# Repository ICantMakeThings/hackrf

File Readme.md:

# Updated USB-C

##### Added USB type C to the pcb, have not eddited anything else.

# HackRF

This repository contains hardware designs and software for HackRF,
a low cost, open source Software Defined Radio platform.

(photo by fd0 from https://github.com/fd0/hackrf-one-pictures)

principal author: Michael Ossmann <mike@ossmann.com>

Information on HackRF and purchasing HackRF: https://greatscottgadgets.com/hackrf/

--------------------

# Documentation

Documentation for HackRF can be viewed on [Read the Docs](https://hackrf.readthedocs.io/en/latest/). The raw documentation files for HackRF are in the [docs folder](https://github.com/mossmann/hackrf/tree/master/docs) in this repository and can be built locally by installing [Sphinx Docs](https://www.sphinx-doc.org/en/master/usage/installation.html) and running `make html`. Documentation changes can be submitted through pull request and suggestions can be made as GitHub issues. 

To create a PDF of the HackRF documentation from the HackRF repository while on Ubuntu:
* run `sudo apt install latexmk texlive-latex-extra`
* navigate to hackrf/docs on command line
* run the command `make latex`
* run the command `make latexpdf`

--------------------

# Getting Help

Before asking for help with HackRF, check to see if your question is listed in the [FAQ](https://hackrf.readthedocs.io/en/latest/faq.html).

For assistance with HackRF general use or development, please look at the [issues on the GitHub project](https://github.com/greatscottgadgets/hackrf/issues). This is the preferred place to ask questions so that others may locate the answer to your question in the future.

We invite you to join our community discussions on [Discord](https://discord.gg/rsfMw3rsU8). Note that while technical support requests are welcome here, we do not have support staff on duty at all times. Be sure to also submit an issue on GitHub if you've found a bug or if you want to ensure that your request will be tracked and not overlooked.

If you wish to see past discussions and questions about HackRF, you may also view the [mailing list archives](https://pairlist9.pair.net/pipermail/hackrf-dev/).

GitHub issues on this repository that are labelled "technical support" by Great Scott Gadgets employees can expect a response time of two weeks. We currently do not have expected response times for other GitHub issues or pull requests for this repository.

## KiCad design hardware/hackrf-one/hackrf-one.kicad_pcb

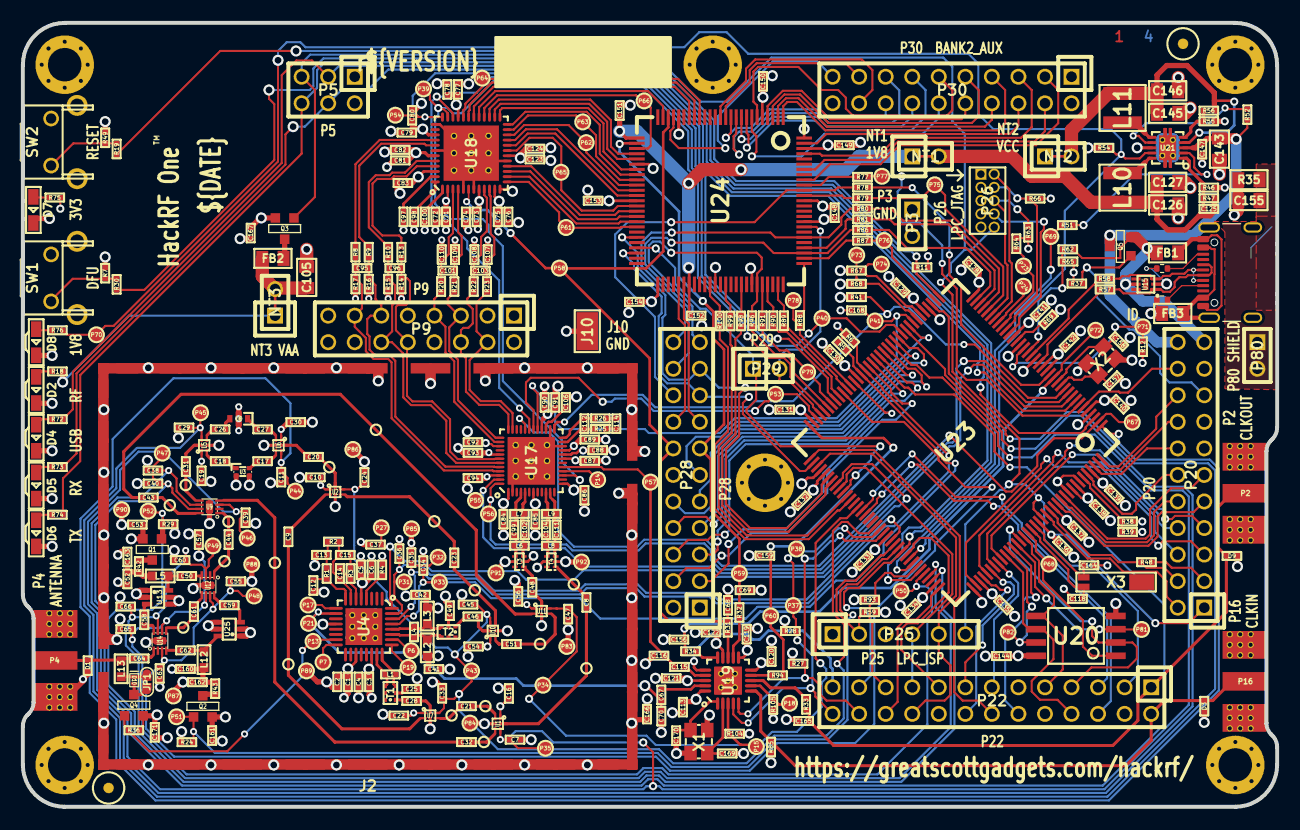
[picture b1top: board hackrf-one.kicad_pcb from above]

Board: 4 copper layers, 120.0 x 75.0 mm, 436 parts (0 on the bottom side), 317 nets.

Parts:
C1, C3, C5, C7, C11, C24, C29, C33, C34, C35, C36, C37, C38, C39, C40, C45, C47, C55, C57, C60, C63, C65, C66, C67, C115, C125: 33pF; GSG-0402
C2, C4, C6, C10, C16, C19, C22, C30, C54, C56, C87, C88, C89, C92, C93, C162, C163: 10nF; GSG-0402
C8, C21, C32, C43, C48, C51, C84, C85, C86, C94, C95, C96, C99, C101, C102, C103, C107, C108, C109, C110: 22pF; GSG-0402
C9, C17, C18, C20, C23, C25, C28, C31, C44, C46, C49, C50, C58, C59, C61, C62, C64, C71, C73, C75, C77, C79, C81, C83, C91, C113, C119, C120, C121, C122, C123, C128, C129, C130, C131, C132, C133, C134, C135, C136, C137, C138, C139, C140, C141, C142, C144, C147, C148, C149, C150, C151, C152, C153, C154, C166, C167: 100nF; GSG-0402
C12, C13: 330pF; GSG-0402
C14: 8p2; GSG-0402
C15, C112: 180pF; GSG-0402
C26, C27, C116, C156: 47pF; GSG-0402
C41, C42, C52, C68, C69, C70, C90, C159, C160, C165, C168: 100pF; GSG-0402
C53, C106, C161, C171: 1uF; GSG-0402
C72, C74, C76, C78, C80, C82, C124: 2.2uF; GSG-0402
C97, C98, C100: 330nF; GSG-0402
C104, C111: 3pF; GSG-0402
C105, C126, C127, C143, C145, C146: 10uF; GSG-0805
C114: 3.3nF; GSG-0402
C118, C157, C158, C164: 18pF; GSG-0402
C155: DNP; GSG-0805
C169, C170: 1.8pF; GSG-0402
D1, D3, D9: GSG-DIODE-TVS-BI; GSG-0402
D2: VAALED; LTST-S220
D4: USBLED; LTST-S220
D5: RXLED; LTST-S220
D6: TXLED; LTST-S220
D7: VCCLED; LTST-S220
D8: 1V8LED; LTST-S220
D10: D_Schottky; DSN1006-2
FB1, FB2, FB3: FILTER; GSG-0805
FID1, FID2: FIDUCIAL; GSG-MARK1MM
J2: RF-SHIELD-FRAME; GSG-SHIELD-BMI-S-230
J4, J5, J6, J7, J8, J9: MOUNTING_HOLE; GSG-HOLE126MIL-COPPER
J10: GND_CLIP; GSG-TEST-POINT-S1751-46R
JP1: Jumper; 0603-JUMPER
L1, L4, L6, L8, L9: DNP; GSG-0402
L2, L3, L5, L12, L13: 10uH; GSG-0603
L7: 6.2nH; GSG-0402
L10, L11: 4u7; GSG-NRG4026
NT1: 1V8; HEADER-1x2-SHORTED
NT2: VCC; HEADER-1x2-SHORTED
NT3: VAA; HEADER-1x2-SHORTED
P2: CLKOUT; GSG-SMA-73251-2120
P3: GND; GSG-HEADER-NOMARK-1x2
P4: ANTENNA; GSG-SMA-73251-2120
P5: LEDS; GSG-HEADER-2x3
P6: GPO4; GSG-TESTPOINT-50MIL
P7: GPO2; GSG-TESTPOINT-50MIL
P9: BASEBAND; GSG-HEADER-2x8
P13: GPO1; GSG-TESTPOINT-50MIL
P14: XCVR_CLKOUT; GSG-TESTPOINT-50MIL
P15: INTR; GSG-TESTPOINT-50MIL
P16: CLKIN; GSG-SMA-73251-2120
P17: GPO6; GSG-TESTPOINT-50MIL
P18: OEB; GSG-TESTPOINT-50MIL
P19: GPO3; GSG-TESTPOINT-50MIL
P20: GPIO; GSG-HEADER-2x11
P21: REF_IN; GSG-TESTPOINT-50MIL
P22: I2S; GSG-HEADER-2x13
P23: DBGEN; GSG-TESTPOINT-50MIL
P24: TRST; GSG-TESTPOINT-50MIL
P25: LPC_ISP; GSG-HEADER-1x6
P26: LPC_JTAG; GSG-50MIL-HEADER-2x5-TH
P27: MIXER_SDATA; GSG-TESTPOINT-50MIL
P28: SD; GSG-HEADER-2x11
P29: CPLD_JTAG; GSG-HEADER-1x2
P30: BANK2_AUX; GSG-HEADER-2x10
P31: MIXER_SCLK; GSG-TESTPOINT-50MIL
P32: MIXER_ENX; GSG-TESTPOINT-50MIL
P33: MIXER_RESETX; GSG-TESTPOINT-50MIL
P34: MIX_BYPASS; GSG-TESTPOINT-50MIL
P35: !MIX_BYPASS; GSG-TESTPOINT-50MIL
P37: SCL; GSG-TESTPOINT-50MIL
P38: SDA; GSG-TESTPOINT-50MIL
P39: SSP1_SCK; GSG-TESTPOINT-50MIL
P40: SSP1_COPI; GSG-TESTPOINT-50MIL
P41: SSP1_CIPO; GSG-TESTPOINT-50MIL
P43: RX; GSG-TESTPOINT-50MIL
P44: HP; GSG-TESTPOINT-50MIL
P45: LP; GSG-TESTPOINT-50MIL
P46: TX_MIX_BP; GSG-TESTPOINT-50MIL
P47: RX_MIX_BP; GSG-TESTPOINT-50MIL
P48: TX_AMP; GSG-TESTPOINT-50MIL
P49: RX_AMP; GSG-TESTPOINT-50MIL
P50: AMP_BYPASS; GSG-TESTPOINT-50MIL
P51: !TX_AMP_PWR; GSG-TESTPOINT-50MIL
P52: !RX_AMP_PWR; GSG-TESTPOINT-50MIL
P53: CS_XCVR; GSG-TESTPOINT-50MIL
P54: CS_AD; GSG-TESTPOINT-50MIL
P55: TXENABLE; GSG-TESTPOINT-50MIL
P56: RXENABLE; GSG-TESTPOINT-50MIL
P57: XTAL2; GSG-TESTPOINT-50MIL
P58: GCK1; GSG-TESTPOINT-50MIL
P59: GCK2; GSG-TESTPOINT-50MIL
P60: SGPIO_CLK; GSG-TESTPOINT-50MIL
P61: DA0; GSG-TESTPOINT-50MIL
P62: DA7; GSG-TESTPOINT-50MIL
P63: DD0; GSG-TESTPOINT-50MIL
P64: DD9; GSG-TESTPOINT-50MIL
P65: DA4; GSG-TESTPOINT-50MIL
P66: DD5; GSG-TESTPOINT-50MIL
P67: RSSI; GSG-TESTPOINT-50MIL
P68: SPIFI_CS; GSG-TESTPOINT-50MIL
P69: VREGMODE; GSG-TESTPOINT-50MIL
P70: EN_1V8; GSG-TESTPOINT-50MIL
P71: ID; GSG-TESTPOINT-50MIL
P72: GP_CLKIN; GSG-TESTPOINT-50MIL
P73: P1_2; GSG-TESTPOINT-50MIL
P74: P1_1; GSG-TESTPOINT-50MIL
P75: SGPIO0; GSG-TESTPOINT-50MIL
P76: SGPIO7; GSG-TESTPOINT-50MIL
P77: SGPIO9; GSG-TESTPOINT-50MIL
P78: SGPIO10; GSG-TESTPOINT-50MIL
P79: SGPIO11; GSG-TESTPOINT-50MIL
P80: SHIELD; GSG-HEADER-NOMARK-1x2
P81: SPIFI_SIO2; GSG-TESTPOINT-50MIL
P82: SPIFI_SIO3; GSG-TESTPOINT-50MIL
P83, P84, P85, P86, P87, P88, P89, P90, P91, P92: GND; GSG-TESTPOINT-50MIL
Q1, Q2, Q3, Q4, Q5: MOSFET_P; SOT23-3
R1, R2, R72, R75: 470; GSG-0402
R3: 22k; GSG-0402
R4: 51k; GSG-0402
R5, R6, R7, R11, R12, R24, R29, R36, R37, R41, R48, R49, R51, R52, R54, R59, R62, R63, R64, R66, R67, R68, R85, R93, R104, R105: 10k; GSG-0402
R8, R9, R10, R13, R73, R76: 1k; GSG-0402
R14, R15, R16, R17: 4k7; GSG-0402
R18, R27, R28, R74: 1k8; GSG-0402
R19, R30, R31, R32, R33, R34, R77, R78, R79, R80, R81, R86, R87, R88, R89, R90, R91, R94, R96, R98, R99, R100: 39; GSG-0402
R20, R21, R22, R23, R57, R58: 0; GSG-0402
R25, R26: 475; GSG-0402
R35: DNP; GSG-0805
R38: 15.4k; GSG-0402
R39, R47: 330k; GSG-0402
R42, R43: 18; GSG-0402
R46, R55: 162k; GSG-0402
R56: 715k; GSG-0402
R65: 18k; GSG-0402
R69: 12k; GSG-0402
SW1: DFU; GSG-SWITCH-FSMRA
SW2: RESET; GSG-SWITCH-FSMRA
T1: MIX_IN_BALUN; GSG-B0310J50100AHF
T2: MIX_OUT_BALUN; GSG-B0310J50100AHF
T3: RX_BALUN; GSG-2500BL14M100
T4: TX_BALUN; GSG-2500BL14M100
TESTPOINT-30MIL-MASKONLY, TESTPOINT-30MIL-MASKONLY#2, TESTPOINT-30MIL-MASKONLY#3, TESTPOINT-30MIL-MASKONLY#4, TESTPOINT-30MIL-MASKONLY#5, TESTPOINT-30MIL-MASKONLY#6, TESTPOINT-30MIL-MASKONLY#7, TESTPOINT-30MIL-MASKONLY#8, TESTPOINT-30MIL-MASKONLY#9, TESTPOINT-30MIL-MASKONLY#10, TESTPOINT-30MIL-MASKONLY#11, TESTPOINT-30MIL-MASKONLY#12, TESTPOINT-30MIL-MASKONLY#13, TESTPOINT-30MIL-MASKONLY#14, TESTPOINT-30MIL-MASKONLY#15, TESTPOINT-30MIL-MASKONLY#16, TESTPOINT-30MIL-MASKONLY#17: VAL**; GSG-TESTPOINT-30MIL-MASKONLY
U1, U2, U5, U6, U7, U10, U11: SKY13453; SKY13350-385LF
U3: LOWPASS_FILTER; GSG-LP0603
U4: RFFC5072; GSG-QFN32
U8: HIGHPASS_FILTER; GSG-HP-DEA
U9, U12, U14: SKY13317; GSG-SKY13317-373LF
U13, U25: MGA-81563; GSG-SOT363
U15: TVS; GSG-LXES1TBCC2-004
U17: MAX2837; GSG-QFN48-6
U18: MAX5864; GSG-QFN48-7
U19: SI5351C; GSG-QFN20-4
U20: W25Q80; GSG-SOIC8-208
U21: TPS62410; GSG-S-PVSON-N10
U23: LPC4320FBD144; GSG-LQFP144
U24: GSG-XC2C64A-7VQG100C; GSG-VQ100
X1: MAIN_XTAL; GSG-XTAL3.2x2.5mm
X2: MCU_XTAL; GSG-XTAL3.2x2.5mm
X3: RTC_XTAL; GSG-XTAL-AB26TRQ

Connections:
!MIX_BYPASS: C7.2, C38.2, P35.1, U1.5 (VCTL), U9.6 (V2), U23.50 (P1_7)
!RX_AMP_PWR: P52.1, Q1.1 (G), R29.2, U23.106 (P2_12)
!TX_AMP_PWR: P51.1, Q2.1 (G), R24.1, U23.97 (P6_9)
!VAA_ENABLE: P5.5, Q3.1 (G), R11.2, U23.37 (P5_0)
+1V8: C151.1, C152.1, NT1.1, U24.26 (VCC), U24.57 (VCC)
/baseband/CLK0: R31.2, U19.13 (CLK0)
/baseband/CLK1: R32.2, U19.12 (CLK1)
/baseband/CLK2: R94.2, U19.9 (CLK2)
/baseband/CLK3: R33.2, U19.8 (CLK3)
/baseband/CLK5: C115.1, U19.17 (CLK5)
/baseband/COM: C97.1, U18.47 (COM)
/baseband/CPOUT+: C112.2, R25.1, U17.23 (CPOUT+)
/baseband/CPOUT-: C112.1, R26.1, U17.24 (CPOUT-)
/baseband/IA+: C101.1, C110.1, R20.1, U18.3 (IA+)
/baseband/IA-: C101.2, C109.1, R21.1, U18.4 (IA-)
/baseband/ID+: R13.1, U18.45 (ID+)
/baseband/ID-: R10.1, U18.44 (ID-)
/baseband/INTR: P15.1, R104.2, U19.3 (INTR)
/baseband/OEB: P18.1, R105.2, U19.7 (OEB)
/baseband/QA+: C103.2, C107.1, R23.1, U18.10 (QA+)
/baseband/QA-: C103.1, C108.1, R22.1, U18.9 (QA-)
/baseband/QD+: R8.1, U18.40 (QD+)
/baseband/QD-: R9.1, U18.41 (QD-)
/baseband/REFN: C98.1, U18.48 (REFN)
/baseband/REFP: C100.1, U18.1 (REFP)
/baseband/RXBBI+: P9.7, R20.2, U17.38 (RXBBI+)
/baseband/RXBBI-: P9.5, R21.2, U17.37 (RXBBI-)
/baseband/RXBBQ+: P9.6, R22.2, U17.36 (RXBBQ+)
/baseband/RXBBQ-: P9.4, R23.2, U17.35 (RXBBQ-)
/baseband/TXBBI+: C96.1, P9.12, R10.2, R15.1, U17.43 (TXBBI+)
/baseband/TXBBI-: C96.2, P9.10, R13.2, R14.1, U17.42 (TXBBI-)
/baseband/TXBBQ+: C95.2, P9.11, R9.2, R16.1, U17.44 (TXBBQ+)
/baseband/TXBBQ-: C95.1, P9.13, R8.2, R17.1, U17.45 (TXBBQ-)
/baseband/XA: C170.2, U19.1 (XA), X1.3
/baseband/XB: C169.2, U19.2 (XB), X1.1
/baseband/XCVR_CLKOUT: P14.1, U17.16 (CLOCKOUT)
/baseband/XTAL2: C115.2, C116.1, P57.1, U17.17 (XTAL2)
/frontend/!ANT_BIAS: P13.1, Q4.1 (G), R36.1, U4.15 (GPO1/ADD1)
/frontend/REF_IN: C67.2, C70.1, P21.1, U4.10 (REF_IN)
/frontend/RX_AMP_IN: C58.1, U14.8 (RF3)
/frontend/RX_AMP_OUT: C50.2, U12.4 (RF1)
/frontend/TX_AMP_IN: C59.1, U12.8 (RF3)
/frontend/TX_AMP_OUT: C62.1, U14.4 (RF1)
/mcu/usb/power/ADC0_0: P20.20, U23.6 (ADC0_0/ADC1_0/DAC)
/mcu/usb/power/ADC0_2: P20.16, U23.143 (ADC0_2/ADC1_2)
/mcu/usb/power/ADC0_3: R38.2, R39.1, U23.139 (ADC0_3/ADC1_3)
/mcu/usb/power/ADC0_5: P20.18, U23.144 (ADC0_5/ADC1_5)
/mcu/usb/power/ADC0_6: P20.14, U23.142 (ADC0_6/ADC1_6)
/mcu/usb/power/B1AUX13: P28.16, U24.55 (BANK1F4M13)
/mcu/usb/power/B1AUX14: P28.15, U24.56 (BANK1F4M14)
/mcu/usb/power/B2AUX1: P30.18, U24.13 (BANK2F1M1)
/mcu/usb/power/B2AUX2: P30.17, U24.12 (BANK2F1M2)
/mcu/usb/power/B2AUX3: P30.16, U24.11 (BANK2F1M3)
/mcu/usb/power/B2AUX4: P30.15, U24.10 (BANK2F1M4)
/mcu/usb/power/B2AUX5: P30.14, U24.9 (BANK2F1M5)
/mcu/usb/power/B2AUX6: P30.13, U24.8 (BANK2F1M6)
/mcu/usb/power/B2AUX7: P30.12, U24.7 (BANK2F1M7)
/mcu/usb/power/B2AUX8: P30.11, U24.6 (BANK2F1M8)
/mcu/usb/power/B2AUX9: P30.10, U24.4 (BANK2F1M9)
/mcu/usb/power/B2AUX10: P30.9, U24.3 (BANK2F1M10)
/mcu/usb/power/B2AUX11: P30.8, U24.2 (BANK2F1M11)
/mcu/usb/power/B2AUX12: P30.7, U24.1 (BANK2F1M12)
/mcu/usb/power/B2AUX13: P30.6, U24.99 (BANK2F1M13)
/mcu/usb/power/B2AUX14: P30.5, U24.97 (BANK2F1M14)
/mcu/usb/power/B2AUX15: P30.4, U24.94 (BANK2F1M15)
/mcu/usb/power/B2AUX16: P30.3, U24.92 (BANK2F1M16)
/mcu/usb/power/BANK2F3M1: R77.2, U24.91 (BANK2F3M1)
/mcu/usb/power/BANK2F3M2: P28.18, R78.2, U24.90 (BANK2F3M2)
/mcu/usb/power/BANK2F3M3: R79.2, U24.89 (BANK2F3M3)
/mcu/usb/power/BANK2F3M4: P28.22, R80.2, U24.81 (BANK2F3M4)
/mcu/usb/power/BANK2F3M5: R81.2, U24.79 (BANK2F3M5)
/mcu/usb/power/BANK2F3M6: P28.20, R86.2, U24.78 (BANK2F3M6)
/mcu/usb/power/BANK2F3M7: R87.2, U24.77 (BANK2F3M7)
/mcu/usb/power/BANK2F3M8: R88.2, U24.76 (BANK2F3M8)
/mcu/usb/power/BANK2F3M9: R89.2, U24.74 (BANK2F3M9)
/mcu/usb/power/BANK2F3M10: R90.2, U24.72 (BANK2F3M10)
/mcu/usb/power/BANK2F3M11: R91.2, U24.71 (BANK2F3M11)
/mcu/usb/power/BANK2F3M12: P28.21, R96.2, U24.70 (BANK2F3M12)
/mcu/usb/power/BANK2F3M14: R98.2, U24.67 (BANK2F3M14)
/mcu/usb/power/BANK2F3M15: R99.2, U24.64 (BANK2F3M15)
/mcu/usb/power/BANK2F3M16: R100.2, U24.61 (BANK2F3M16)
/mcu/usb/power/CPLD_TCK: P28.17, U23.74 (P6_1), U24.48 (TCK)
/mcu/usb/power/CPLD_TDI: P28.19, U23.78 (P6_2), U24.45 (TDI)
/mcu/usb/power/CPLD_TDO: P29.2, U23.69 (P9_5), U24.83 (TDO)
/mcu/usb/power/CPLD_TMS: P29.1, U23.82 (P6_5), U24.47 (TMS)
/mcu/usb/power/DBGEN: P23.1, R64.1, U23.28 (DBGEN)
/mcu/usb/power/DM: R58.1, U23.20 (USB0_DM)
/mcu/usb/power/DP: R57.1, U23.18 (USB0_DP)
/mcu/usb/power/EN1V8: P70.1, R54.2, R76.2, U21.9 (EN2), U23.100 (P6_10)
/mcu/usb/power/GCK0: P30.19, U24.22 (BANK1F2M7)
/mcu/usb/power/GPIO3_8: P20.5, U23.110 (P7_0)
/mcu/usb/power/GPIO3_9: P20.6, U23.113 (P7_1)
/mcu/usb/power/GPIO3_10: P20.7, U23.115 (P7_2)
/mcu/usb/power/GPIO3_11: P20.8, U23.117 (P7_3)
/mcu/usb/power/GPIO3_12: P20.9, U23.132 (P7_4)
/mcu/usb/power/GPIO3_13: P20.10, U23.133 (P7_5)
/mcu/usb/power/GPIO3_14: P20.11, U23.134 (P7_6)
/mcu/usb/power/GPIO3_15: P20.12, U23.140 (P7_7)
/mcu/usb/power/GP_CLKIN: C156.1, P72.1, R34.1, U23.14 (P4_7)
/mcu/usb/power/I2C1_SCL: P22.5, U23.88 (P2_4)
/mcu/usb/power/I2C1_SDA: P22.6, U23.87 (P2_3)
/mcu/usb/power/I2S0_RX_MCLK: P22.14, U23.73 (P6_0)
/mcu/usb/power/I2S0_RX_SCK: P22.12, U23.120 (PF_4)
/mcu/usb/power/I2S0_RX_SDA: P22.13, U23.116 (P3_2)
/mcu/usb/power/I2S0_RX_WS: P22.15, U23.114 (P3_1)
/mcu/usb/power/I2S0_TX_MCLK: P22.17, U23.99 (CLK2)
/mcu/usb/power/I2S0_TX_SCK: P22.16, U23.112 (P3_0)
/mcu/usb/power/ISP: P25.2, R59.2, U23.96 (P2_7)
/mcu/usb/power/LED1: P5.3, R72.2, U23.3 (P4_1)
/mcu/usb/power/LED2: P5.4, R73.2, U23.8 (P4_2)
/mcu/usb/power/LED3: P5.6, R74.2, U23.103 (P6_12)
/mcu/usb/power/P1_1: P74.1, R67.1, U23.42 (P1_1)
/mcu/usb/power/P1_2: P73.1, R68.1, U23.43 (P1_2)
/mcu/usb/power/P2_8: P22.23, R30.1, U23.98 (P2_8)
/mcu/usb/power/P2_9: P22.21, R93.1, U23.102 (P2_9)
/mcu/usb/power/P2_13: P22.22, U23.108 (P2_13)
/mcu/usb/power/REG_OUT1: C145.2, C146.2, L11.1, NT2.2, R56.1, U21.4 (FB1)
/mcu/usb/power/REG_OUT2: C125.1, C126.1, C127.1, L10.2, NT1.2, R47.1
/mcu/usb/power/RESET: P22.3, P25.6, P26.10, R19.1, U23.128 (RESET)
/mcu/usb/power/RREF: R69.1, U23.24 (USB0_RREF)
/mcu/usb/power/RTCX1: C118.1, U23.125 (RTCX1), X3.2
/mcu/usb/power/RTCX2: C164.1, U23.126 (RTCX2), X3.1
/mcu/usb/power/RTC_ALARM: P20.2, U23.129 (RTC_ALARM)
/mcu/usb/power/SD_CD: P28.3, U23.60 (P1_13)
/mcu/usb/power/SD_CLK: P28.11, U23.45 (CLK0)
/mcu/usb/power/SD_CMD: P28.9, U23.49 (P1_6)
/mcu/usb/power/SD_DAT0: P28.7, U23.52 (P1_9)
/mcu/usb/power/SD_DAT1: P28.6, U23.53 (P1_10)
/mcu/usb/power/SD_DAT2: P28.5, U23.55 (P1_11)
/mcu/usb/power/SD_DAT3: P28.4, U23.56 (P1_12)
/mcu/usb/power/SD_POW: P28.10, U23.48 (P1_5)
/mcu/usb/power/SD_VOLT0: P28.8, U23.51 (P1_8)
/mcu/usb/power/SGPIO0: P75.1, R79.1, U23.32 (P0_0)
/mcu/usb/power/SGPIO1: R81.1, U23.34 (P0_1)
/mcu/usb/power/SGPIO2: R89.1, U23.62 (P1_15)
/mcu/usb/power/SGPIO3: R90.1, U23.64 (P1_16)
/mcu/usb/power/SGPIO4: R98.1, U23.79 (P6_3)
/mcu/usb/power/SGPIO5: R99.1, U23.83 (P6_6)
/mcu/usb/power/SGPIO6: R100.1, U23.84 (P2_2)
/mcu/usb/power/SGPIO7: P76.1, R87.1, U23.38 (P1_0)
/mcu/usb/power/SGPIO9: P77.1, R77.1, U23.7 (P4_3)
/mcu/usb/power/SGPIO10: P78.1, R88.1, U23.61 (P1_14)
/mcu/usb/power/SGPIO11: P79.1, R91.1, U23.66 (P1_17)
/mcu/usb/power/SGPIO12: R96.1, U23.67 (P1_18)
/mcu/usb/power/SGPIO13: R78.1, U23.15 (P4_8)
/mcu/usb/power/SGPIO14: R80.1, U23.33 (P4_9)
/mcu/usb/power/SGPIO15: R86.1, U23.35 (P4_10)
/mcu/usb/power/SPIFI_CIPO: P22.7, U20.2 (DO), U23.122 (P3_6)
/mcu/usb/power/SPIFI_COPI: P22.9, U20.5 (DI), U23.123 (P3_7)
/mcu/usb/power/SPIFI_CS: P68.1, U20.1 (CS), U23.124 (P3_8)
/mcu/usb/power/SPIFI_SCK: P22.8, U20.6 (CLK), U23.118 (P3_3)
/mcu/usb/power/SPIFI_SIO2: P81.1, U20.3 (WP), U23.121 (P3_5)
/mcu/usb/power/SPIFI_SIO3: P82.1, U20.7 (HOLD), U23.119 (P3_4)
/mcu/usb/power/TCK: P26.4, R66.2, U23.27 (TCK/SWDCLK)
/mcu/usb/power/TDI: P26.8, U23.26 (TDI)
/mcu/usb/power/TDO: P26.6, R63.1, U23.31 (TDO/SWO)
/mcu/usb/power/TMS: P26.2, U23.30 (TMS/SWDIO)
/mcu/usb/power/U0_RXD: P22.19, P25.4, U23.81 (P2_1)
/mcu/usb/power/U0_TXD: P22.20, P25.5, U23.75 (P2_0)
/mcu/usb/power/USB_SHIELD: C155.1, P80.1, P80.2, R35.1
/mcu/usb/power/VBAT: C136.1, P20.1, U23.127 (VBAT)
/mcu/usb/power/VBUS: FB1.2, P20.21, Q5.2 (S), R62.2, U15.5 (VDD)
/mcu/usb/power/VBUSCTRL: P20.17, Q5.1 (G), R37.2
/mcu/usb/power/VIN: C143.1, C147.1, P20.22, Q5.3 (D), R52.1, U21.3 (VIN)
/mcu/usb/power/VREGMODE: P69.1, R51.2, U23.101 (P6_11)
/mcu/usb/power/WAKEUP: P20.4, R48.2, U23.130 (WAKEUP0)
/mcu/usb/power/XTAL1: C157.1, U23.12 (XTAL1), X2.1
/mcu/usb/power/XTAL2: C158.1, U23.13 (XTAL2), X2.3
AMP_BYPASS: C57.1, C65.2, P50.1, U12.6 (V2), U14.6 (V2), U23.104 (P2_10)
CLK6: P22.25, U19.16 (CLK6)
CLKIN: D3.2 (K), P16.1 (RF), P22.2, R85.1, U19.6 (CLKIN)
CLKOUT: C165.1, D9.2 (K), P2.1 (RF), P22.1, R33.1
CS_AD: P54.1, U18.36 (CS), U23.65 (P5_7)
CS_XCVR: P53.1, U17.30 (CS), U23.70 (P1_20)
DA0: P61.1, U18.13 (DA0), U24.43 (BANK1F4M8)
DA1: U18.14 (DA1), U24.42 (BANK1F4M7)
DA2: U18.15 (DA2), U24.41 (BANK1F4M6)
DA3: U18.16 (DA3), U24.40 (BANK1F4M5)
DA4: P65.1, U18.19 (DA4), U24.39 (BANK1F4M4)
DA5: U18.20 (DA5), U24.37 (BANK1F4M3)
DA6: U18.21 (DA6), U24.36 (BANK1F4M2)
DA7: P62.1, U18.22 (DA7), U24.35 (BANK1F4M1)
DD0: P63.1, U18.23 (DD0), U24.34 (BANK1F2M16)
DD1: U18.24 (DD1), U24.33 (BANK1F2M15)
DD2: U18.25 (DD2), U24.32 (BANK1F2M14)
DD3: U18.26 (DD3), U24.30 (BANK1F2M13)
DD4: U18.27 (DD4), U24.29 (BANK1F2M12)
DD5: P66.1, U18.28 (DD5), U24.28 (BANK1F2M11)
DD6: U18.29 (DD6), U24.24 (BANK1F2M9)
DD7: U18.30 (DD7), U24.19 (BANK1F2M6)
DD8: U18.31 (DD8), U24.18 (BANK1F2M5)
DD9: P64.1, U18.32 (DD9), U24.17 (BANK1F2M4)
GCK1: C68.1, P28.14, P58.1, R31.1, U18.6 (CLK), U24.23 (BANK1F2M8)
GCK2: C69.1, P28.13, P59.1, R32.1, U24.27 (BANK1F2M10)
GND: C1.2, C2.2, C3.2, C4.2, C5.2, C6.2, C7.1, C10.1, C11.1, C12.2, C13.2, C16.2, C19.1, C22.1, C24.1, C25.2, C29.2, C30.2, C33.2, C34.2, C35.2, C36.2, C37.2, C38.1, C39.1, C40.1, C41.2, C42.2, C45.1, C47.1, C49.1, C52.2, C53.2, C54.2, C55.2, C56.2, C57.2, C60.1, C63.2, C65.1, C66.1, C68.2, C69.2, C70.2, C71.2, C72.2, C73.2, C74.2, C75.2, C76.2, C77.2, C78.2, C79.2, C80.2, C81.2, C82.2, C83.2, C84.2, C85.2, C86.2, C87.2, C88.2, C89.2, C90.2, C91.2, C92.2, C93.2, C94.2, C97.2, C98.2, C100.2, C105.2, C106.2, C107.2, C108.2, C109.2, C110.2, C113.2, C116.2, C118.2, C119.2, C120.2, C121.2, C122.2, C123.2, C124.2, C126.2, C127.2, C128.2, C129.2, C130.2, C131.2, C132.2, C133.2, C134.2, C135.2, C136.2, C137.2, C138.2, C139.2, C140.2, C141.2, C142.2, C143.2, C144.2, C145.1, C146.1, C147.2, C148.2, C149.2, C150.2, C151.2, C152.2, C153.2, C154.2, C155.2, C156.2, C157.2, C158.2, C159.2, C160.2, C161.2, C162.1, C163.1, C164.2, C165.2, C166.2, C167.2, C168.2, C169.1, C170.1, C171.2, D1.1 (A), D2.1 (K), D3.1 (A), D4.1 (K), D5.1 (K), D6.1 (K), D7.1 (K), D8.1 (K), D9.1 (A), FB3.2, J2.0 (SHIELD), J4.1, J5.1, J6.1, J7.1, J8.1, J9.1, J10.1, P2.2 (GND), P3.1, P3.2, P4.2 (GND), P5.1, P9.1, P9.2, P9.3, P9.8, P9.9, P9.14, P9.15, P9.16, P16.2 (GND), P20.13, P20.15, P20.19, P22.4, P22.10, P22.18, P25.1, P26.3, P26.5, P26.9, P28.2, P28.12, P30.2, P30.20, P83.1, P84.1, P85.1, P86.1, P87.1, P88.1, P89.1, P90.1, P91.1, P92.1, R4.1, R7.2, R14.2, R15.2, R16.2, R17.2, R35.2, R37.1, R39.2, R41.1, R46.1, R54.1, R55.1, R65.1, R68.2, R69.2, R85.2, R93.2, SW1.0 (SHIELD), SW2.0 (SHIELD), SW2.1, T3.2 (PC), T3.5 (S2), T4.2 (PC), T4.5 (S2), U1.3 (GND), U2.3 (GND), U3.2 (GND), U3.3 (GND), U4.0 (EP), U4.12 (TM), U5.3 (GND), U6.3 (GND), U7.3 (GND), U8.2 (GND), U8.4 (GND), U9.0 (GND), U10.3 (GND), U11.3 (GND), U12.0 (GND), U13.1 (GND), U13.2 (GND), U13.4 (GND), U13.5 (GND), U14.0 (GND), U15.2 (GND), U17.0 (EP), U17.2 (GNDRXLNA), U17.22 (GNDCP), U17.26 (GNDVCO), U18.0 (EP), U18.5 (GND), U18.7 (GND), U18.12 (GND), U18.17 (OGND), U18.37 (GND), U18.42 (GND), U19.0 (GND), U20.4 (GND), U21.0 (PP), U21.8 (GND), U23.4 (VSSIO), U23.19 (USB0_VSSA_TERM), U23.23 (USB0_VSSA_REF), U23.40 (VSSIO), U23.76 (VSSIO), U23.109 (VSSIO), U23.135 (VSSA), U23.138 (ADC0_4/ADC1_4), U24.21 (GND), U24.31 (GND), U24.62 (GND), U24.69 (GND), U24.84 (GND), U24.100 (GND), U25.1 (GND), U25.2 (GND), U25.4 (GND), U25.5 (GND), X1.2, X1.4, X2.2, X2.4
HP: C11.2, P44.1, U6.5 (VCTL), U23.1 (P4_0)
LP: C29.1, P45.1, U5.5 (VCTL), U23.39 (P5_1)
MCU_CLK: R34.2, U19.15 (CLK7)
MIXER_ENX: C35.1, P32.1, R6.2, U4.30 (ENX), U23.57 (P5_4)
MIXER_RESETX: C34.1, P33.1, R5.2, U4.29 (RESETX), U23.58 (P5_5)
MIXER_SCLK: C36.1, P31.1, U4.31 (SCLK), U23.95 (P2_6)
MIXER_SDATA: C37.1, P27.1, U4.32 (SDATA), U23.80 (P6_4)
MIX_BYPASS: C47.2, P34.1, U11.5 (VCTL), U23.86 (P6_8)
MIX_CLK: C67.1, U19.19 (CLK4)
unnamed: C8.2, U1.6 (RFC)
unnamed: C9.1, U7.2 (RF1)
unnamed: C9.2, U2.2 (RF1)
unnamed: C12.1, R1.2, U4.8 (LFILT3)
unnamed: C13.1, R1.1, R2.2
unnamed: C14.1, C15.1, R2.1, U4.7 (LFITLT2)
unnamed: C14.2, R3.1, U4.6 (LFILT1)
unnamed: C15.2, R3.2
unnamed: C17.1, U3.4 (IN)
unnamed: C17.2, U6.4 (RF2)
unnamed: C18.1, U5.2 (RF1)
unnamed: C18.2, U3.1 (OUT)
unnamed: C20.1, U6.6 (RFC)
unnamed: C20.2, U2.6 (RFC)
unnamed: C21.1, U1.2 (RF1)
unnamed: C21.2, U7.4 (RF2)
unnamed: C23.1, U10.4 (RF2)
unnamed: C23.2, U2.4 (RF2)
unnamed: C25.1, T1.2 (S2)
unnamed: C26.1, U8.3 (OUT)
unnamed: C26.2, U5.4 (RF2)
unnamed: C27.1, U8.1 (IN)
unnamed: C27.2, U6.2 (RF1)
unnamed: C28.1, T1.1 (S1)
unnamed: C28.2, U7.6 (RFC)
unnamed: C31.1, U9.5 (RF2)
unnamed: C31.2, U5.6 (RFC)
unnamed: C32.1, U1.4 (RF2)
unnamed: C32.2, U9.4 (RF1)
unnamed: C43.1, U9.8 (RF3)
unnamed: C43.2, U11.2 (RF1)
unnamed: C44.1, U12.1 (RFC)
unnamed: C44.2, U9.1 (RFC)
unnamed: C46.1, U10.6 (RFC)
unnamed: C46.2, T2.1 (S1)
unnamed: C48.1, U11.6 (RFC)
unnamed: C49.2, T2.2 (S2)
unnamed: C50.1, L5.2, U13.6 (OUT)
unnamed: C51.1, U11.4 (RF2)
unnamed: C51.2, U10.2 (RF1)
unnamed: C58.2, U13.3 (IN)
unnamed: C59.2, U25.3 (IN)
unnamed: C61.1, U14.5 (RF2)
unnamed: C61.2, U12.5 (RF2)
unnamed: C62.2, L12.2, U25.6 (OUT)
unnamed: C64.1, U14.1 (RFC)
unnamed: C64.2, D1.2 (K), L13.2, P4.1 (RF)
unnamed: C99.1, L7.1, U17.4 (RXRF+)
unnamed: C99.2, L6.1, T3.4 (PR2)
unnamed: C102.1, L7.2, U17.5 (RXRF-)
unnamed: C102.2, L6.2, T3.3 (PR1)
unnamed: C104.1, L9.1, U17.10 (TXRF+)
unnamed: C104.2, L8.1, T4.4 (PR2)
unnamed: C105.1, FB2.2, NT3.2
unnamed: C106.1, U17.27 (BYPASS)
unnamed: C111.1, L9.2, U17.11 (TXRF-)
unnamed: C111.2, L8.2, T4.3 (PR1)
unnamed: C114.1, R26.2
unnamed: C114.2, R25.2
unnamed: C125.2, R46.2, R47.2, U21.1 (ADJ2)
unnamed: C160.1, C162.2, L12.1, R43.1
unnamed: C52.1, C163.2, L5.1, R42.2
unnamed: D2.2 (A), R18.1
unnamed: D4.2 (A), R72.1
unnamed: D5.2 (A), R73.1
unnamed: D6.2 (A), R74.1
unnamed: D7.2 (A), R75.1
unnamed: D8.2 (A), R76.1
unnamed: D10.1 (K), JP1.1 (A), L13.1
unnamed: D10.2 (A), JP1.2 (B), Q4.3 (D)
unnamed: FB2.1, Q3.3 (D)
unnamed: R58.2, U15.3 (ESD2)
unnamed: R57.2, U15.1 (ESD1)
unnamed: P71.1, R12.2, U23.22 (USB0_ID)
unnamed: L1.1, T1.4 (PR2), U4.23 (MIX_IPP)
unnamed: L1.2, T1.3 (PR1), U4.24 (MIX_IPN)
unnamed: L2.1, L4.2, T2.4 (PR2), U4.27 (MIX_OPN)
unnamed: L3.1, L4.1, T2.3 (PR1), U4.28 (MIX_OPP)
unnamed: L10.1, U21.10 (SW2)
unnamed: L11.2, U21.6 (SW1)
unnamed: P6.1, U4.26 (GPO4/LD/DO)
unnamed: P7.1, U4.16 (GPO2/ADD2)
unnamed: P17.1, U4.9 (MODE/GPO6)
unnamed: P19.1, U4.25 (GPO3/FM)
unnamed: P24.1, U23.29 (TRST)
unnamed: Q1.3 (D), R42.1
unnamed: Q2.3 (D), R43.2
unnamed: R4.2, U4.4 (REXT)
unnamed: R19.2, R49.2, SW2.2
unnamed: R7.1, R30.2, SW1.2
unnamed: R51.1, U21.2 (MODE/DATA)
unnamed: R52.2, U21.7 (EN1)
unnamed: R55.2, R56.2, U21.5 (DEF1)
unnamed: R62.1, R65.2, U23.21 (USB0_VBUS)
RSSI: P67.1, U17.32 (RSSI), U23.2 (ADC0_1/ADC1_1)
RX: C24.2, C33.1, C45.2, P43.1, U2.5 (VCTL), U7.5 (VCTL), U10.5 (VCTL), U23.91 (P2_5)
RXENABLE: P56.1, U17.48 (RXENABLE), U23.10 (P4_5)
RX_AMP: C60.2, C66.2, P49.1, U12.3 (V1), U14.7 (V3), U23.105 (P2_11)
RX_IF: C48.2, T3.1 (S1)
RX_MIX_BP: C40.2, P47.1, U9.7 (V3), U23.54 (P5_3)
SCL: P22.26, P37.1, R28.2, U19.4 (SCL), U23.92 (I2C0_SCL)
SDA: P22.24, P38.1, R27.2, U19.5 (SDA), U23.93 (I2C0_SDA)
SGPIO_CLK: C159.1, P60.1, R94.1, U23.72 (P9_6)
SSP1_CIPO: C168.1, P41.1, U17.29 (DOUT), U23.44 (P1_3)
SSP1_COPI: P40.1, U17.31 (DIN), U18.34 (DIN), U23.47 (P1_4)
SSP1_SCK: P39.1, U17.15 (SCLK), U18.35 (SCLK), U23.68 (P1_19)
TXENABLE: P55.1, U17.47 (TXENABLE), U23.9 (P4_4)
TX_AMP: C55.1, C63.1, P48.1, U12.7 (V3), U14.3 (V1), U23.63 (P5_6)
TX_IF: C8.1, T4.1 (S1)
TX_MIX_BP: C39.2, P46.1, U9.3 (V1), U23.46 (P5_2)
VAA: C3.1, C4.1, C5.1, C6.1, C10.2, C16.1, C19.2, C22.2, C30.1, C41.1, C42.1, C53.1, C54.1, C56.1, C71.1, C72.1, C73.1, C74.1, C75.1, C76.1, C77.1, C78.1, C79.1, C80.1, C81.1, C82.1, C83.1, C84.1, C85.1, C86.1, C87.1, C89.1, C90.1, C91.1, C92.1, C93.1, C94.1, C161.1, C166.1, C171.1, L2.2, L3.2, NT3.1, Q1.2 (S), Q2.2 (S), Q4.2 (S), R18.2, R24.2, R29.1, R36.2, U1.1 (VDD), U2.1 (VDD), U4.5 (ANA_VDD1), U4.22 (ANA_VDD2), U5.1 (VDD), U6.1 (VDD), U7.1 (VDD), U10.1 (VDD), U11.1 (VDD), U17.1 (VCCRXLNA), U17.7 (VCCTXPAD), U17.13 (VCCTXMX), U17.19 (VCCXTAL), U17.21 (VCCCP), U17.28 (VCCVCO), U17.39 (VCCRXVGA), U17.41 (VCCRXFL), U17.46 (VCCRXMX), U18.2 (VDD), U18.8 (VDD), U18.11 (VDD), U18.33 (VDD), U18.39 (VDD), U18.43 (VDD), U18.46 (REFIN)
VCC: C1.1, C2.1, C88.1, C113.1, C119.1, C120.1, C121.1, C122.1, C123.1, C124.1, C128.1, C129.1, C130.1, C131.1, C132.1, C133.1, C134.1, C135.1, C137.1, C138.1, C139.1, C140.1, C141.1, C142.1, C144.1, C148.1, C149.1, C150.1, C153.1, C154.1, C167.1, NT2.1, P5.2, P20.3, P22.11, P26.1, P28.1, P30.1, Q3.2 (S), R5.1, R6.1, R11.1, R12.1, R27.1, R28.1, R38.1, R48.1, R49.1, R59.1, R63.2, R64.2, R66.1, R67.2, R75.2, R104.1, R105.1, SW1.1, U4.19 (DIG_VDD), U17.20 (VCCDIG), U18.18 (OVDD), U19.10 (VDDOB), U19.11 (VDDOA), U19.14 (VDDOD), U19.18 (VDDOC), U19.20 (VDD), U20.8 (VCC), U23.5 (VDDIO), U23.16 (USB0_VDDA3V3_DRIVER), U23.17 (USB0_VDDA3V3), U23.25 (VDDREG), U23.36 (VDDIO), U23.41 (VDDIO), U23.59 (VDDREG), U23.71 (VDDIO), U23.77 (VDDIO), U23.94 (VDDREG), U23.107 (VDDIO), U23.111 (VDDIO), U23.131 (VDDREG), U23.136 (ADC0_7/ADC1_7), U23.137 (VDDA), U23.141 (VDDIO), U24.5 (VAUX), U24.38 (VCCIO1), U24.51 (VCCIO1), U24.88 (VCCIO2), U24.98 (VCCIO2)
XCVR_EN: R41.2, U17.25 (ENABLE), U23.11 (P4_6)

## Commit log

2024-07-04 Updated to USB-C
    Updated to USB-C

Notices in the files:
parts and their libraries:
COPYRIGHT: Copyright 2012-2023 Great Scott Gadgets
LICENSE: Licensed under the CERN-OHL-P v2
